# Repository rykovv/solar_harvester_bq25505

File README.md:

# Solar Harvester v1.0_m1

Solar harvesting power supply board based on TI BQ25505 PMIC with MPPT functionality configured for tracking 80% of the PV input. The board provides voltage/current measurement IC (INA226) intended for measurement of the PV input and a fuel gauge system based on MAX17040 IC to check and monitor battery state.

## Table of Contents ##

[[_TOC_]]

## Rev1 manufactured and assembled

## Rev2 simulated

## Detailed Overview

The BQ25505 was created for special needs of ultra low power applications. Therefore, it is designed for extract uW and mW of power generated from multiple energy harvesting sources. The board configuration suits only for solar power applications.

Once a PV pannel and Lipo battery are connected to the board and load capacitors are charged (>=1.8V) the main boost charger starts working extracting energy from the PV pannel. The ouput power is driven based on VBAT_OK threshold (3.3V) which is set based on R~ok1-3~ resistors. If the attached battery voltage is less then VBAT_OK, than only charging circuitry will work. This way the battery is saved from being damaged by undervoltage condition. Once the battery voltage rises up to VBAT_OK_HYST (3.7V), the load will be connected to the battery again. The BQ25505 provides overvoltage protection functionality set based on R~ov1,2~ resistors. That is, when the battery voltage reaches VBAT_OV voltage (4.2V) the main boost charger cease charging and only monitors voltage levels. Summing up, the BQ25505 will charge the storage element always unless its voltage is less than VBAT_OV. Refer to the Battery over-voltage, under-voltage and operating range section for examining concrete values calculation.

There is a possibility for supercap input energy storage instead of the Lipo battery. The maximum voltage for the supercap must be 5V. This modification implies changes in VBAT_OK, VBAT_OK_HYST, and VBAT_OV threasholds; and R~ok1-3~ resistors must be reselected accordingly. Refer to the BQ25505 datasheet to see corresponding formulas and equations (Section 8.2.1.2 Detailed Design Procedure).

Adjust CSTOR load capacitors depending on energy storage voltage. Remove C11 if VBAT_SEC < 3.0V.

## Specifications

Input:
 - PV panel 5V, 150mA
 - Lipo 3.7V battery

Output:
 - 3.3V, 1.2A
 - 5V, 1.8A

Maximum charging curerrent is 100mA.

## ICs
 - BQ25505
 - TPS613221A (3.3V)
 - TPS613222A (5V)
 - INA226
 - MAX17040
 - DMP3085LSD (dual pmos)

## Data Out - I^2^C
In order to extract information from the voltage/current measurement IC and the fuel gauge the proper I^2^C connection is needed. External pin headers fulfill this purpose. Note the internal I^2^C bus is **not pulled up**. Make sure the I^2^C bus from your main MCU board pulls up the bus.

## Battery over-voltage, under-voltage and operating range

### Over-voltage

Battery over-voltage protection is determined by R1 and R2 resistors according to 7.3.3

**VBAT_OV** = 3/2 * VBIAS * (1 + R1/R2)

Since, VBIAS is internally set to 1.21V, we have

VBAT_OV = 3/2 * 1.21V * (1 + 7.32M/5.62M) = **4.179V ~= 4.2V**

### Under-voltage

Battery under-voltage is internally set to 1.95V (see 7.3.2), hence being to suitable for the application, the push-pull multiplexer drivers (see 7.3.5) were used for the purpose. According to VBAT_OK and VBAT_OK_HYST values (see Operating range section).

### Operating range

The battery operating range is established by R3, R4, and R5 resistors which determine VBAT_OK and VBAT_OK_HYST values. According to the selected resistors values,

**VBAT_OK** = VBIAS * (1 + R4/R5) = 1.21V * (1 + 7.5M/4.3M) = **3.32V**

and

**VBAT_OK_HYST** = VBIAS * (1 + [R4 + R3]/R5) = 1.21V * (1 + [7.5M + 1.2M]/4.3M) = **3.658V**

## Issues

Despite all values of resistors R~ok1-3~ and R~ov1,2~ were correctly calculated (see 3.7V 860mAh Li-po battery and Battery over-voltage, under-voltage and operating range section) BQ25505 does not behave as expected and presents serious instabilities incompatible with deployment in real applications. When the battery is fully charged and attached, on one hand, and there is enough PV power input to start the circuitry, on the other hand, the BQ25505 starts working as expected until the battery is discharged (voltage below VBAT_OK). When the battery is half-discharged (voltage about VBAT_OK_HYST), and independently of the PV power input, VSTOR is unable to give stable output. What happens is when the 3.3V & 5V voltage regulators reach predefined output levels and the load starts to consume power (especially when the power is greater than 200mA, perhaps max transitory current in this state is much lower), the BQ25505 switches constantly on and off #VBAT_SEC_ON for a couple of milliseconds. It makes impossible to provide enough power for stable MCU launching.

A potential solution for this drawback is to substitute the current Under-voltage protection scheme with a battery management IC that would be in charge of over- and under-voltage protection.

## Revisions

### Rev 0
### Rev 1
 - Components with 0603 metric footprint were substituted by 0603 imperial
### Rev 2
 - Board size increased to 30x55
 - Changed C3 footprint to 3528, C4 and C11 to 1608
 - Changed C9 and C10 to 100u 3528
 - Rewired PCB
 - Components font size increased to 32mil

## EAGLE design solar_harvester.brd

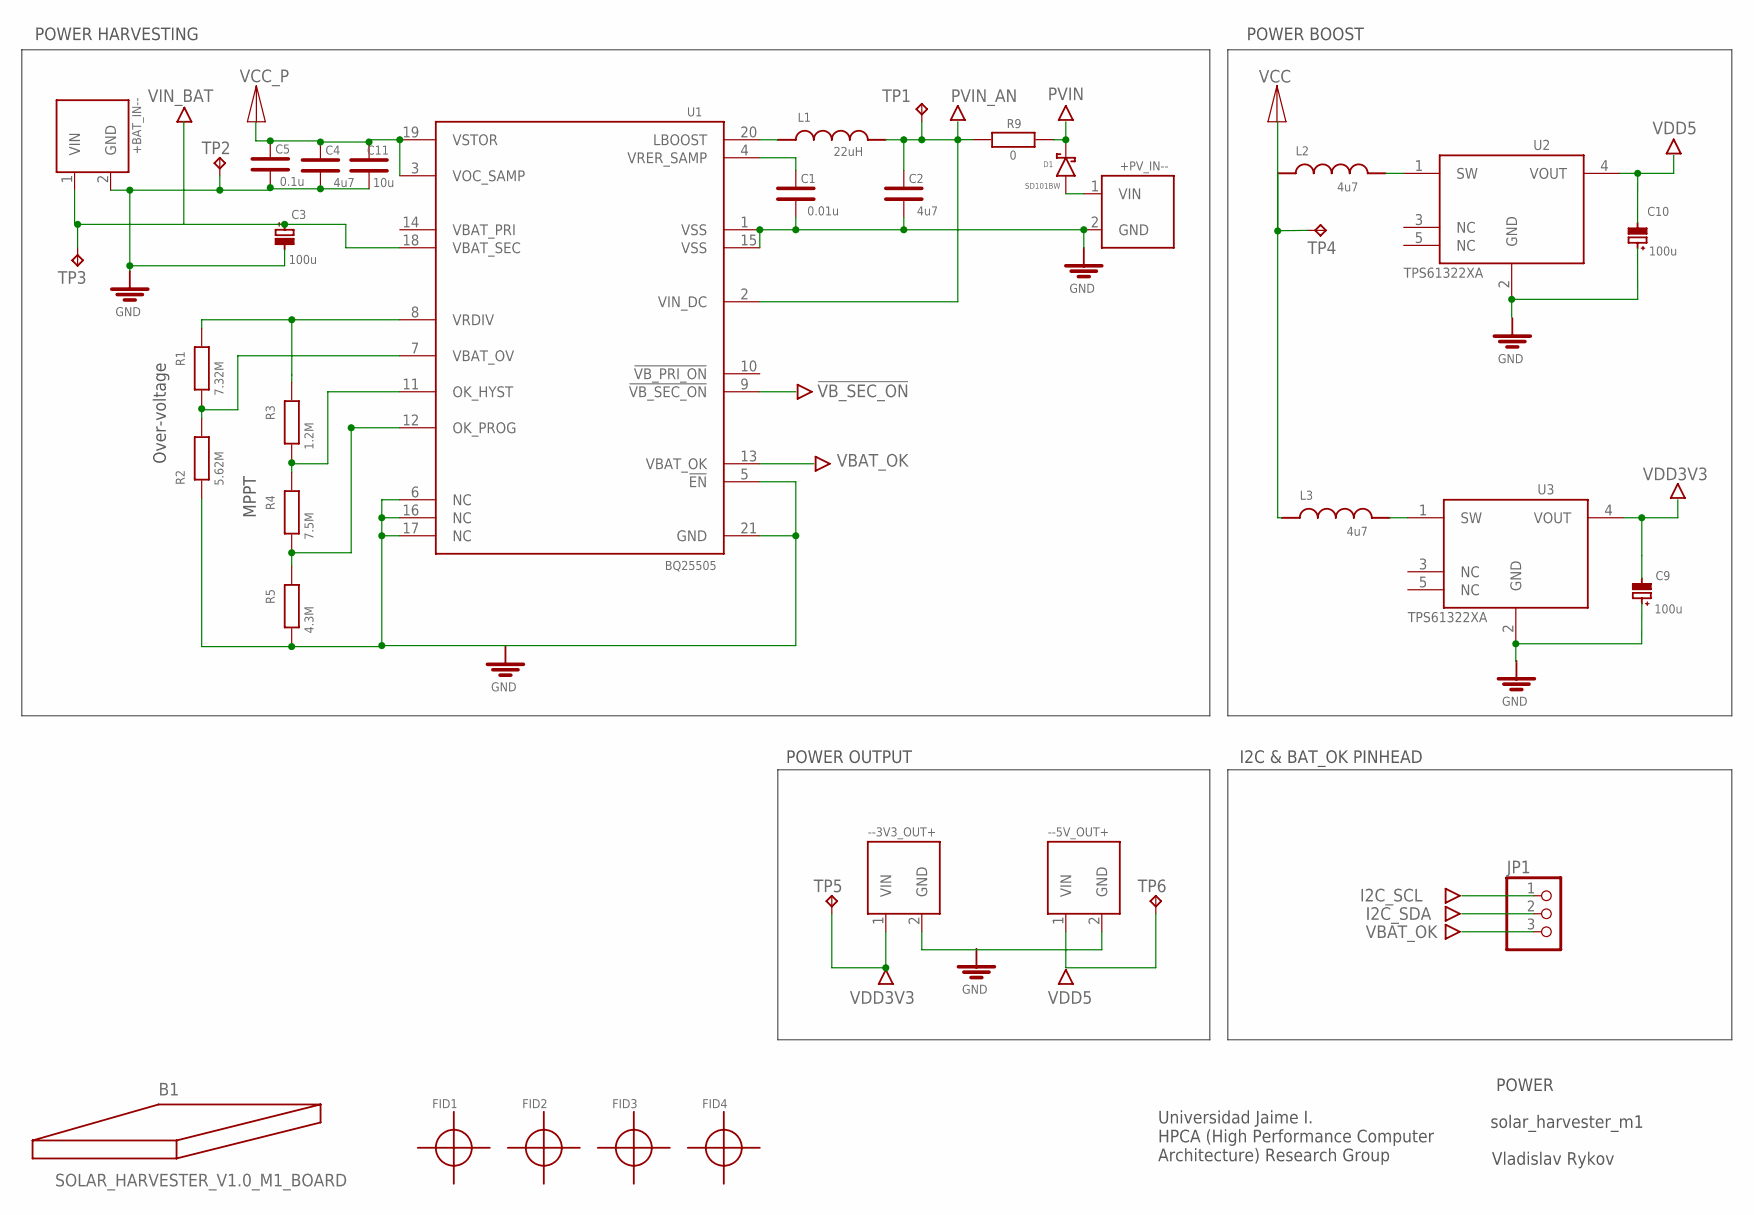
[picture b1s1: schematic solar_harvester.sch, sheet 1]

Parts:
+BAT_IN--: CONN_SCEW_TYPE_2P; CONN_SCREW_TYPE_2P
+PV_IN--: CONN_SCEW_TYPE_2P; CONN_SCREW_TYPE_2P
--3V3_OUT+, --5V_OUT+: CONN_SCEW_TYPE_2P; CONN_SCREW_TYPE_2P
B1: SOLAR_HARVESTER_V1.0_M1_BOARD; SOLAR_HARVESTER_V1.0_M1_FOOTPRINT
C1: 0.01u; 1608_FOOTPRINT
C2, C4: 4u7; 1608_FOOTPRINT
C3, C9, C10: 100u; 3528_TAN_FOOTPRINT
C5: 0.1u; 1608_FOOTPRINT
C11: 10u; 1608_FOOTPRINT
D1: SD101BW; SOD-123
FID1, FID2, FID3, FID4: FIDUCIAL_25
JP1: PINHD-1X3; 1X03
L1: 22uH; FIXED_4040_FOOTPRINT
L2: 4u7; FIXED_5050_FOOTPRINT
L3: 4u7; FIXED_2520_FOOTPRINT
R1: 7.32M; RESISTOR_1608_FOOTPRINT
R2: 5.62M; RESISTOR_1608_FOOTPRINT
R3: 1.2M; RESISTOR_1608_FOOTPRINT
R4: 7.5M; RESISTOR_1608_FOOTPRINT
R5: 4.3M; RESISTOR_1608_FOOTPRINT
R9: 0; RESISTOR_1608_FOOTPRINT
TP1, TP2, TP3, TP4, TP5, TP6: TPTP10SQ; TP10SQ
U1: BQ25505; BQ25505_FOOTPRINT
U2, U3: TPS61322XA; TPS61322XA_FOOTPRINT

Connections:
!VB_SEC_ON!: U1.9 (!VB_SEC_ON!); also elsewhere on the board
GND: +BAT_IN--.2 (GND), +PV_IN--.2 (GND), --3V3_OUT+.2 (GND), --5V_OUT+.2 (GND), C1.2, C2.2, C3.2, C4.2, C5.2, C9.1, C10.1, C11.2, R2.1, R5.1, TP2.TP, U1.1 (VSS), U1.5 (!EN!), U1.6 (NC), U1.15 (VSS), U1.16 (NC), U1.17 (NC), U1.21 (GND), U2.2 (GND), U3.2 (GND); also elsewhere on the board
I2C_SCL: JP1.1; also elsewhere on the board
I2C_SDA: JP1.2; also elsewhere on the board
unnamed: L1.1, U1.20 (LBOOST)
unnamed: C1.1, U1.4 (VRER_SAMP)
unnamed: R1.2, R3.2, U1.8 (VRDIV)
unnamed: R1.1, R2.2, U1.7 (VBAT_OV)
unnamed: R3.1, R4.2, U1.11 (OK_HYST)
unnamed: R4.1, R5.2, U1.12 (OK_PROG)
unnamed: +PV_IN--.1 (VIN), D1.2
unnamed: L3.2, U3.1 (SW)
unnamed: L2.2, U2.1 (SW)
PVIN: D1.1, R9.2; also elsewhere on the board
PVIN_AN: C2.1, L1.2, R9.1, TP1.TP, U1.2 (VIN_DC); also elsewhere on the board
VBAT_OK: JP1.3, U1.13 (VBAT_OK)
VCC: L2.1, L3.1, TP4.TP; also elsewhere on the board
VCC_P: C4.1, C5.1, C11.1, U1.3 (VOC_SAMP), U1.19 (VSTOR); also elsewhere on the board
VDD3V3: --3V3_OUT+.1 (VIN), C9.2, TP5.TP, U3.4 (VOUT)
VDD5: --5V_OUT+.1 (VIN), C10.2, TP6.TP, U2.4 (VOUT)
VIN_BAT: +BAT_IN--.1 (VIN), C3.1, TP3.TP, U1.18 (VBAT_SEC); also elsewhere on the board

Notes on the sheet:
POWER HARVESTING
POWER BOOST
POWER
solar_harvester_m1
Universidad Jaime I. HPCA (High Performance Computer Architecture) Research Group
Vladislav Rykov
I2C & BAT_OK PINHEAD
POWER OUTPUT
Over-voltage
MPPT

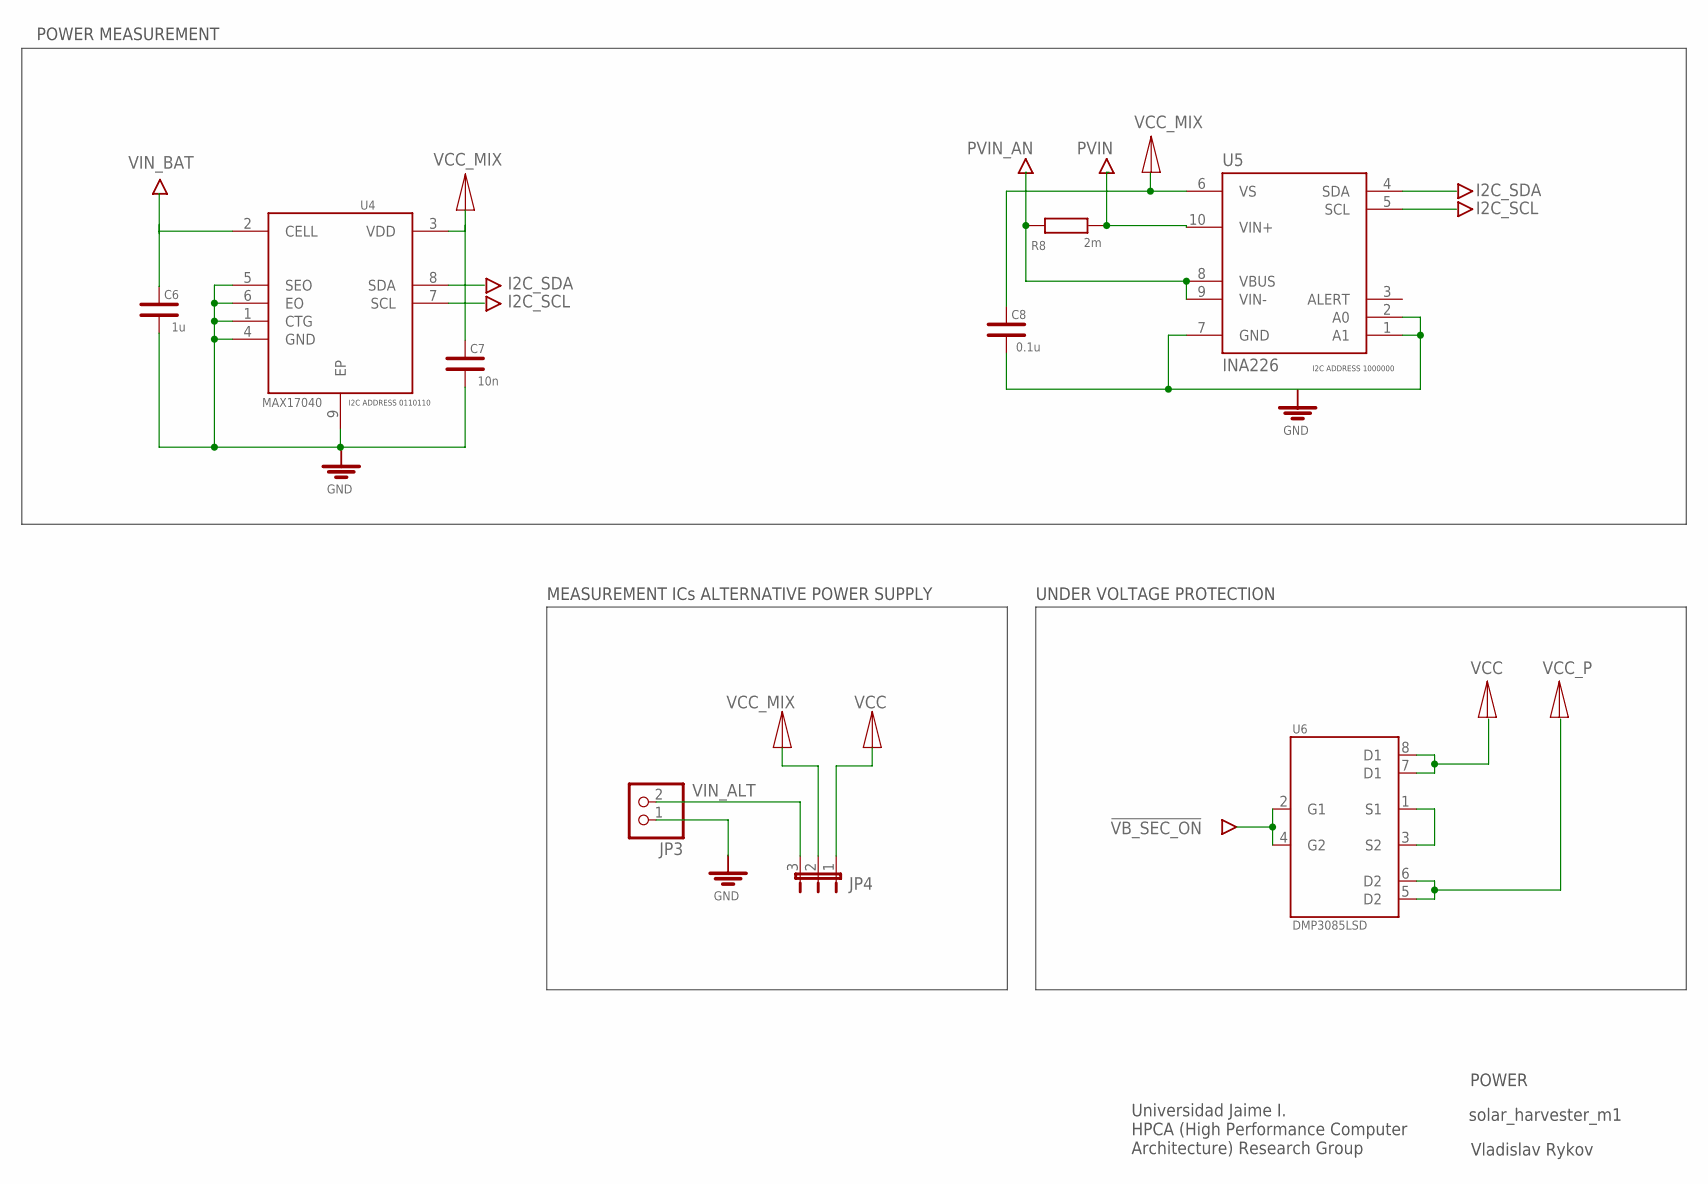
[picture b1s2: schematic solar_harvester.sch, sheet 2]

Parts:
C6: 1u; 1608_FOOTPRINT
C7: 10n; 1608_FOOTPRINT
C8: 0.1u; 1608_FOOTPRINT
JP3: PINHD-1X2; 1X02
JP4: JP2E; JP2
R8: 2m; RESISTOR_2012_FOOTPRINT
U4: MAX17040; MAX17040G+T_FOOTPRINT
U5: INA226; INA226_FOOTPRINT
U6: DMP3085LSD; SO-8

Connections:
!VB_SEC_ON!: U6.2 (G1), U6.4 (G2); also elsewhere on the board
GND: C6.2, C7.2, C8.2, JP3.1, U4.1 (CTG), U4.4 (GND), U4.5 (SEO), U4.6 (EO), U4.9 (EP), U5.1 (A1), U5.2 (A0), U5.7 (GND); also elsewhere on the board
I2C_SCL: U4.7 (SCL), U5.5 (SCL); also elsewhere on the board
I2C_SDA: U4.8 (SDA), U5.4 (SDA); also elsewhere on the board
unnamed: U6.1 (S1), U6.3 (S2)
PVIN: R8.2, U5.10 (VIN+); also elsewhere on the board
PVIN_AN: R8.1, U5.8 (VBUS), U5.9 (VIN-); also elsewhere on the board
VCC: JP4.1, U6.7 (D1), U6.8 (D1); also elsewhere on the board
VCC_MIX: C7.1, C8.1, JP4.2, U4.3 (VDD), U5.6 (VS)
VCC_P: U6.5 (D2), U6.6 (D2); also elsewhere on the board
VIN_ALT: JP3.2, JP4.3
VIN_BAT: C6.1, U4.2 (CELL); also elsewhere on the board

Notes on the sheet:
I2C ADDRESS 1000000
POWER
solar_harvester_m1
POWER MEASUREMENT
I2C ADDRESS 0110110
Universidad Jaime I. HPCA (High Performance Computer Architecture) Research Group
Vladislav Rykov
UNDER VOLTAGE PROTECTION
MEASUREMENT ICs ALTERNATIVE POWER SUPPLY

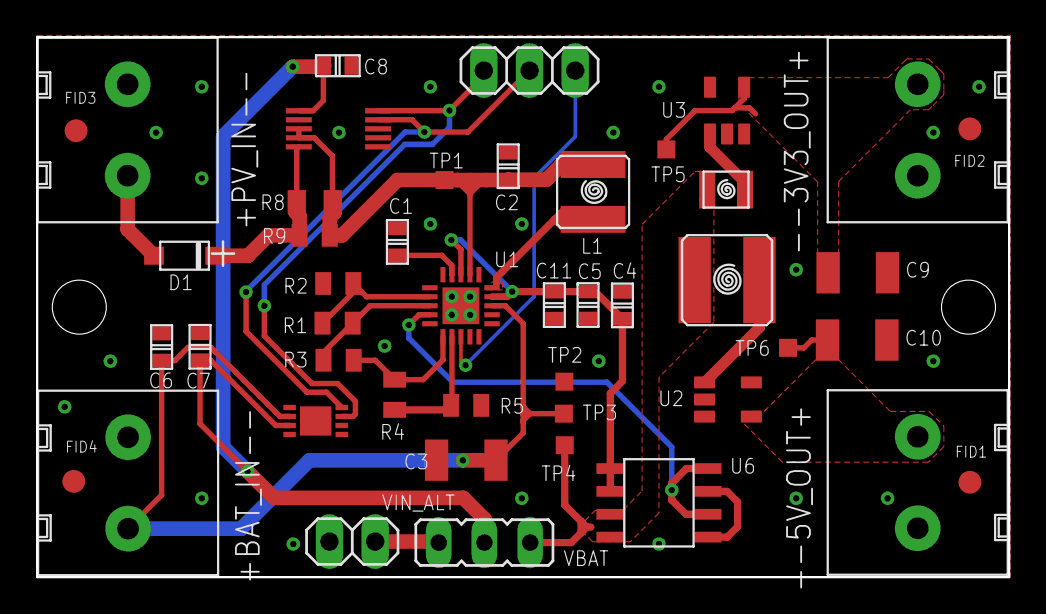
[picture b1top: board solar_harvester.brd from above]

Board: 2 copper layers, 54.0 x 30.0 mm, 46 parts (0 on the bottom side), 24 nets.

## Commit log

2019-11-27 schematic complete v01. Caps and diode selection needed
2019-11-28 board routing started
2019-11-29 bq25505, both tps622, max17004 routed
2019-12-02 routing complete without battery under-voltage protection
2019-12-02 resized board, routing almost finished
2019-12-02 Routing done, without uv protection
2019-12-02 uv added schematic
2019-12-02 uv routed done
2019-12-03 readme added
2019-12-03 checked pad sizes, embellished board
2019-12-11 tps, fids added, todo:rev gnd, pass grc
2019-12-11 alt measurement ics vin added, drc & gnd rev done
2019-12-13 input power signs added
2019-12-16 final BOM Rev0 composed, layout adjust
    Some caps sizes were changed due to vol/dimension issues
2020-01-15 BOM revised, gerbers generated
2020-01-21 desc minor modif
2020-03-05 increase comps sizes -> pcb reruting (in progress)
2020-03-05 rerouting finished
2020-03-09 Rev 1 done. todo: bom update
2020-03-09 BOM updated
2020-09-22 BOM+gerbers update, DESC added
2020-11-02 readme.md extended after assembling & testing
2020-11-19 Rev2
